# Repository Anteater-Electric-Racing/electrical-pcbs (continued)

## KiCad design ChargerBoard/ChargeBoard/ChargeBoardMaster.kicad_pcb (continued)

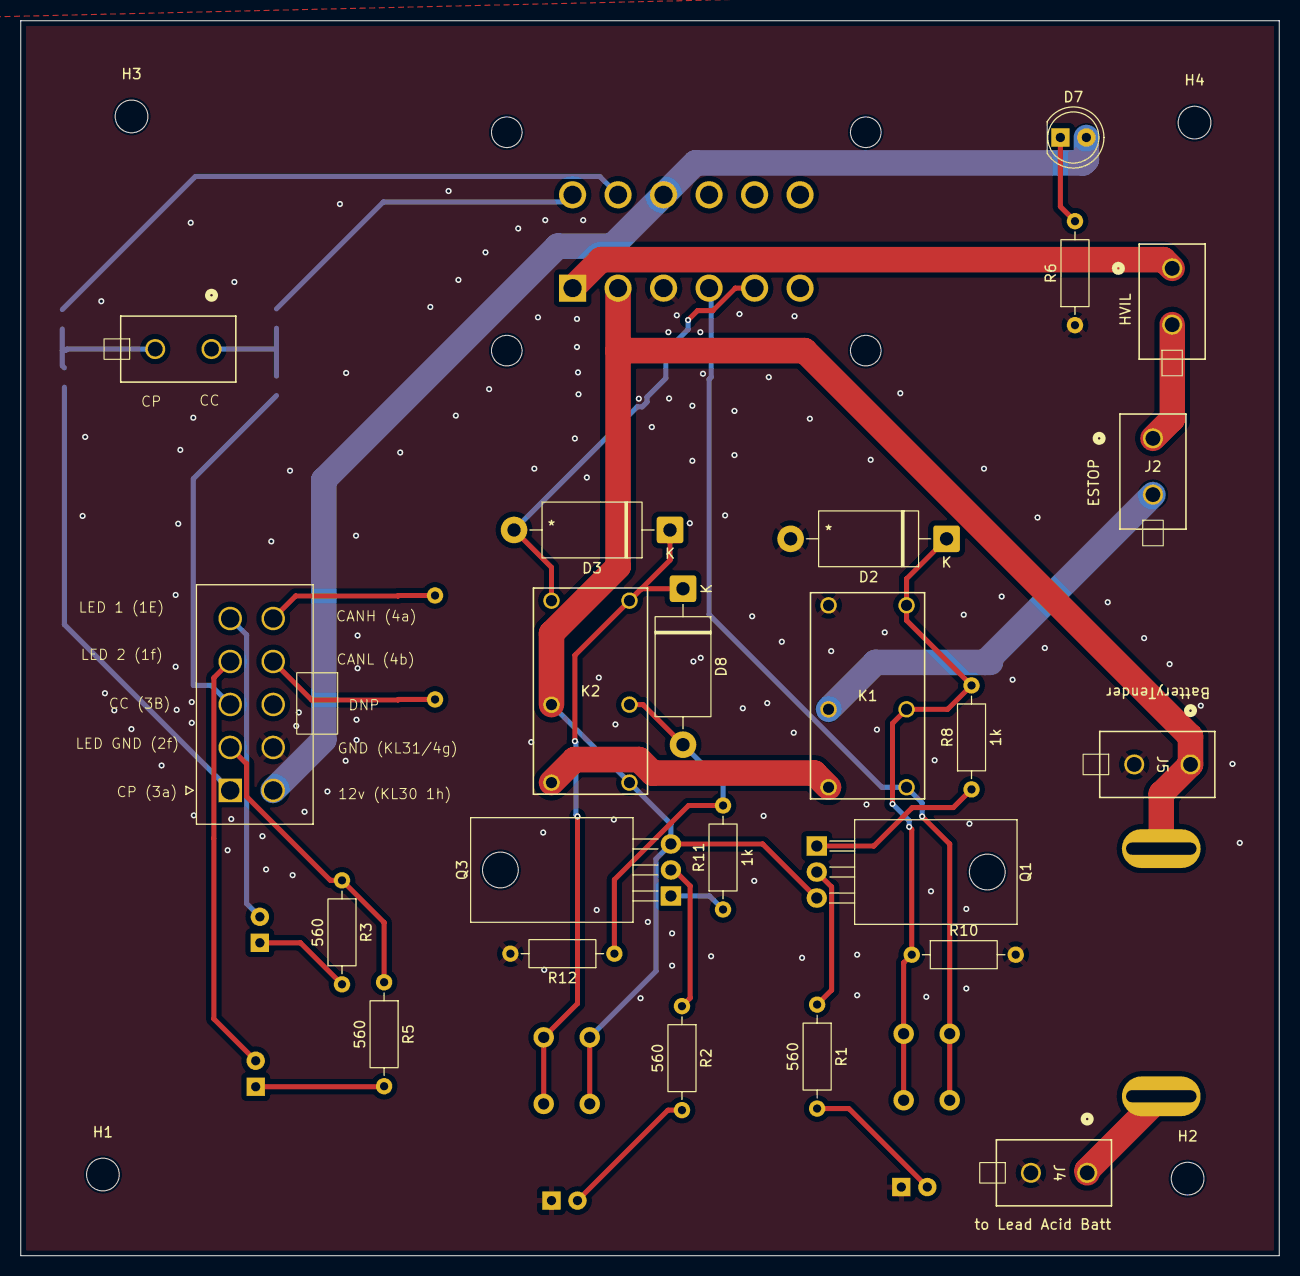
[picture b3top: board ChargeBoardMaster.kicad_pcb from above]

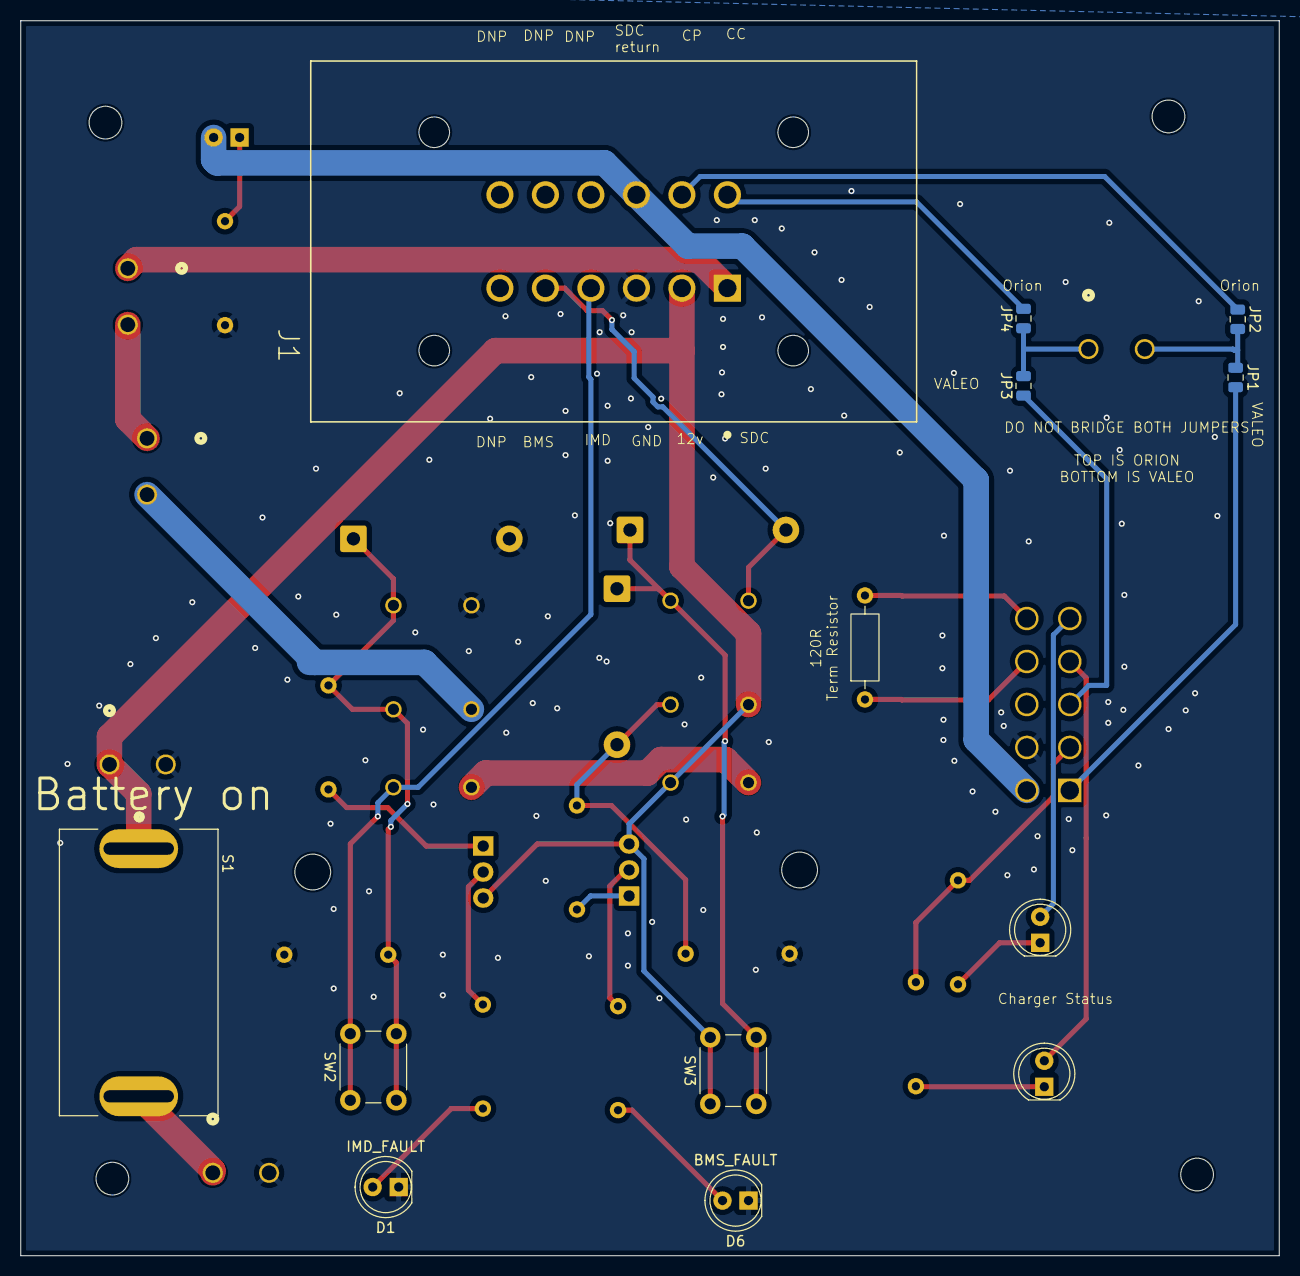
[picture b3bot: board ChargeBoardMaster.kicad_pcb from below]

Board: 2 copper layers, 123.0 x 120.7 mm, 40 parts (13 on the bottom side), 33 nets.

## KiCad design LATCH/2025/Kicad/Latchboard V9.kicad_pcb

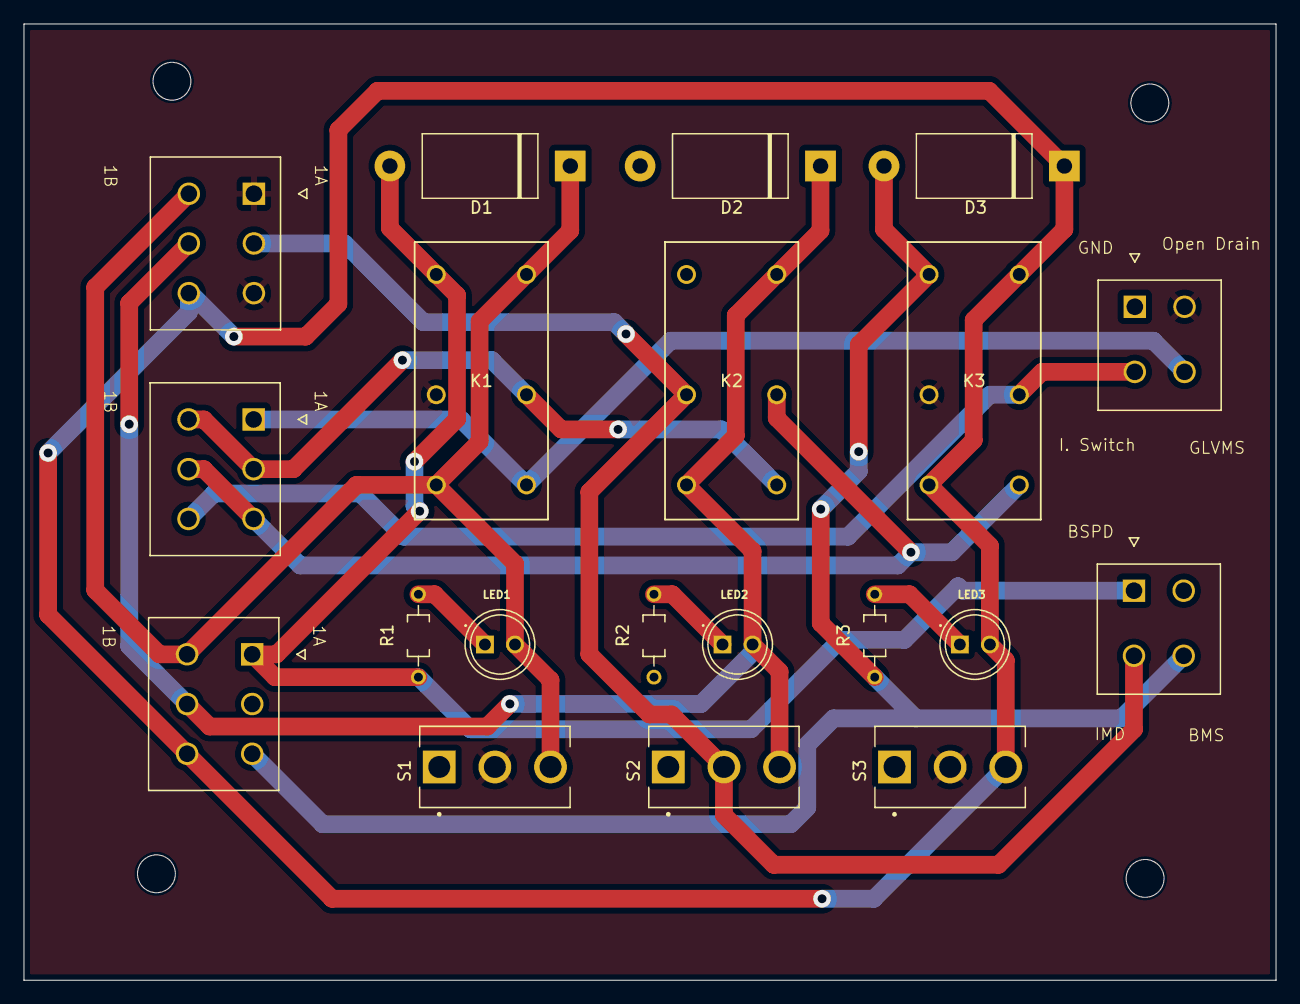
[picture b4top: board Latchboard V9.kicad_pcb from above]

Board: 2 copper layers, 105.8 x 80.8 mm, 20 parts (0 on the bottom side), 15 nets.

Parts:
D1, D2, D3: D; P2_DO-201
J1, J2: 2x2 Conn; MOLEX_39296048
J3: Relay Switch Connections; MOLEX_39288060
J4: Relay Debug Connections; MOLEX_39288060
J5: Relay LED Connections; MOLEX_39288060
K1, K2, K3: DPST Relay NO; CONN_P6B-26P_OMR
LED1, LED2, LED3: Debug LED; LED_WP7113ID
R1: THT 1k; RESAD700W45L350D185
R2, R3: THT 1K; RESAD700W45L350D185
S1, S2, S3: SPDT Switch NO; SW_100SP1T1B4M2QE

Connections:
+12V: J1.2, J3.1, J3.3, K1.3, K3.3, S1.2, S3.2
/DEBUG 1A: J1.4, J4.1, K1.5
/DEBUG 1B: J4.2, J4.4, K1.6, K2.5
/DEBUG 2B: J4.3, J4.5, K2.6, K3.5
/DEBUG 3B: J1.3, J4.6, K3.6
/LED 1B: D1.1 (K), J3.4, J5.4, K1.4, K1.8, LED1.A, S1.3
/LED 2B: D2.1 (K), J3.5, J5.5, K2.4, K2.8, LED2.A, S2.3
/LED 3B: D3.1 (K), J3.6, J5.6, K3.4, K3.8, LED3.A, S3.3
BMS FAULT: D3.2 (A), J2.4, J5.3, K3.1, R3.1
BSPD Fault: D1.2 (A), J2.1, J5.1, K1.1, R1.1
GND: D2.2 (A), J1.1, J5.2, K2.1, R2.1
IMD FAULT: J2.3, J3.2, K2.3, S2.2
unnamed: LED1.C, R1.2
unnamed: LED2.C, R2.2
unnamed: LED3.C, R3.2

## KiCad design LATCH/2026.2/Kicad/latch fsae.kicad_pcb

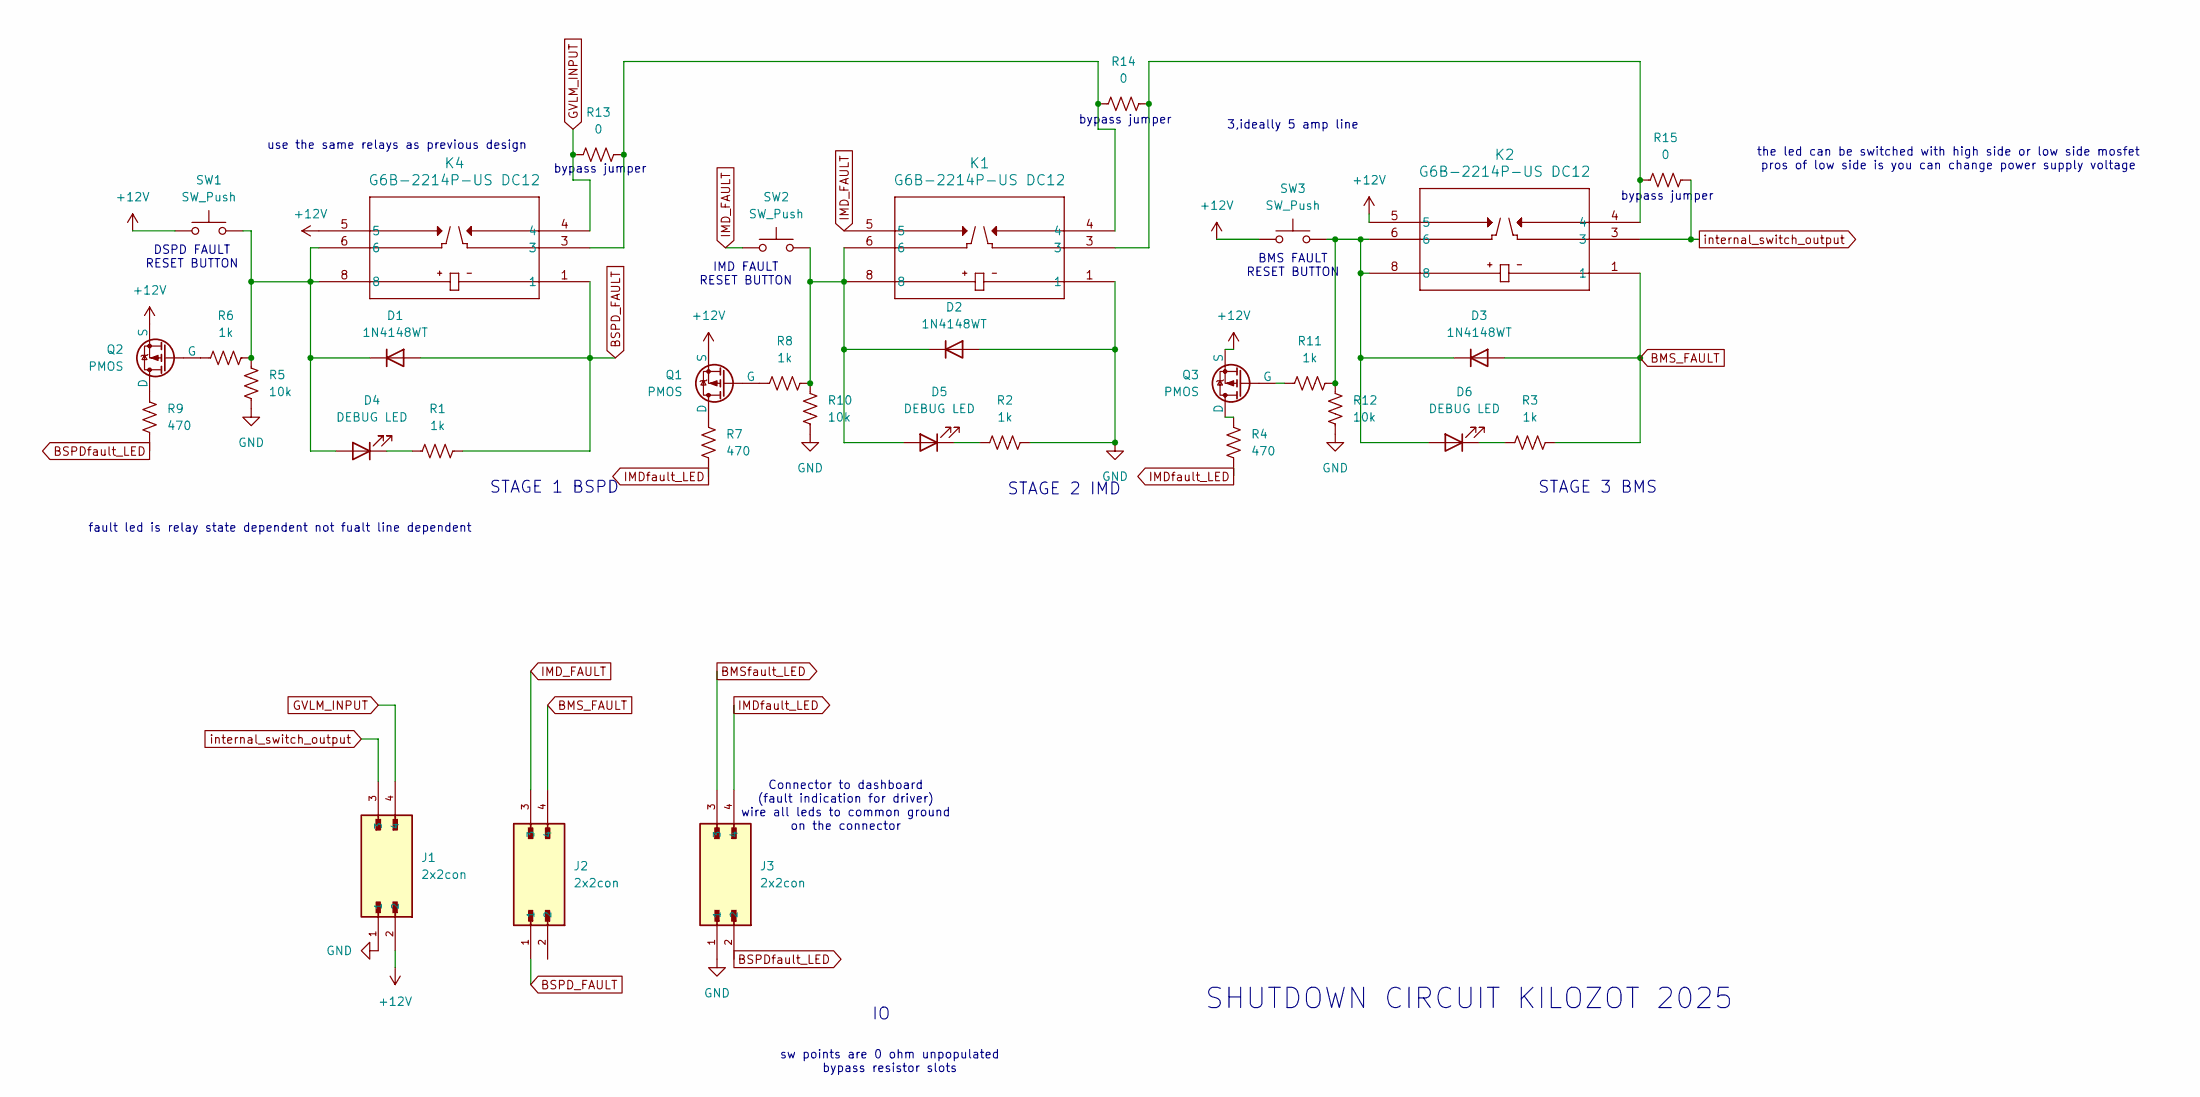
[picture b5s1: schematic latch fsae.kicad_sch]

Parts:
D1, D2, D3: 1N4148WT; D_DO-201_P15.24mm_Horizontal
D4, D5, D6: DEBUG LED; LED_D5.0mm
J1, J2, J3: 2x2con; MOLEX_39296048; PARTREV M4
K1, K2, K4: G6B-2214P-US DC12; RELAY_G6B-2114P-US_OMR
Q1, Q2, Q3: PMOS; TO-220-3_Vertical
R1, R2, R3, R6, R8, R11: 1k; R_Axial_DIN0207_L6.3mm_D2.5mm_P10.16mm_Horizontal
R4, R7, R9: 470; R_Axial_DIN0207_L6.3mm_D2.5mm_P10.16mm_Horizontal
R5, R10, R12: 10k; R_Axial_DIN0207_L6.3mm_D2.5mm_P10.16mm_Horizontal
R13, R14, R15: 0; R_Axial_DIN0207_L6.3mm_D2.5mm_P10.16mm_Horizontal
SW1, SW2, SW3: SW_Push; SW_PUSH_6mm

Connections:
+12V: J1.2, K2.5, K4.5, Q1.3 (S), Q2.3 (S), Q3.3 (S), SW1.1, SW3.1
BMS_FAULT: D3.2 (A), J2.4, K2.1, R3.2
BMSfault_LED: J3.3
BSPD_FAULT: D1.2 (A), J2.1, K4.1, R1.2
BSPDfault_LED: J3.2, R9.1
GND: D2.2 (A), J1.1, J3.1, K1.1, R2.2, R5.2, R10.2, R12.2
GVLM_INPUT: J1.4, K4.4, R13.1
IMD_FAULT: J2.3, K1.5, SW2.1
IMDfault_LED: J3.4, R4.1, R7.1
unnamed: D1.1 (K), D4.2 (A), K4.6, K4.8, R5.1, R6.1, SW1.2
unnamed: D2.1 (K), D5.2 (A), K1.6, K1.8, R8.2, R10.1, SW2.2
unnamed: D3.1 (K), D6.2 (A), K2.6, K2.8, R11.2, R12.1, SW3.2
unnamed: D4.1 (K), R1.1
unnamed: D5.1 (K), R2.1
unnamed: D6.1 (K), R3.1
unnamed: K1.3, K2.4, R14.2, R15.1
unnamed: K1.4, K4.3, R13.2, R14.1
unnamed: Q1.2 (D), R7.2
unnamed: Q1.1 (G), R8.1
unnamed: Q2.2 (D), R9.2
unnamed: Q2.1 (G), R6.2
unnamed: Q3.2 (D), R4.2
unnamed: Q3.1 (G), R11.1
internal_switch_output: J1.3, K2.3, R15.2

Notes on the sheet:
Connector to dashboard (fault indication for driver) wire all leds to common ground on the connector
3,ideally 5 amp line
bypass jumper
DSPD FAULT RESET BUTTON
the led can be switched with high side or low side mosfet pros of low side is you can change power supply voltage
fault led is relay state dependent not fualt line dependent
STAGE 1 BSPD
sw points are 0 ohm unpopulated bypass resistor slots
SHUTDOWN CIRCUIT KILOZOT 2025
use the same relays as previous design
IMD FAULT RESET BUTTON
STAGE 3 BMS
STAGE 2 IMD
BMS FAULT RESET BUTTON

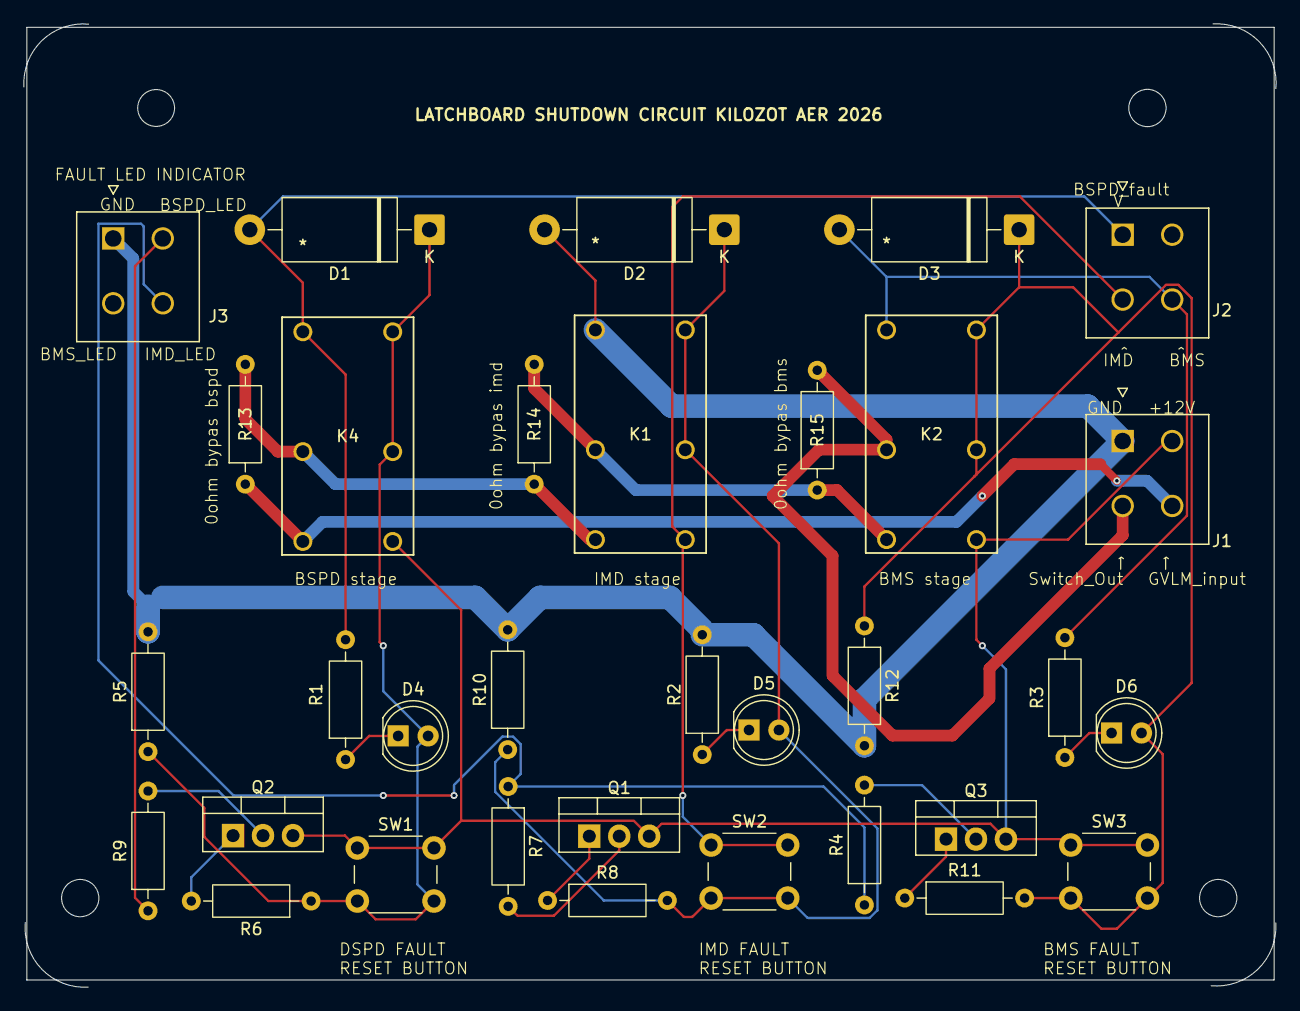
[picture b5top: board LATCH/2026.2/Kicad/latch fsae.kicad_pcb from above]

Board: 2 copper layers, 106.2 x 81.7 mm, 33 parts (0 on the bottom side), 23 nets.

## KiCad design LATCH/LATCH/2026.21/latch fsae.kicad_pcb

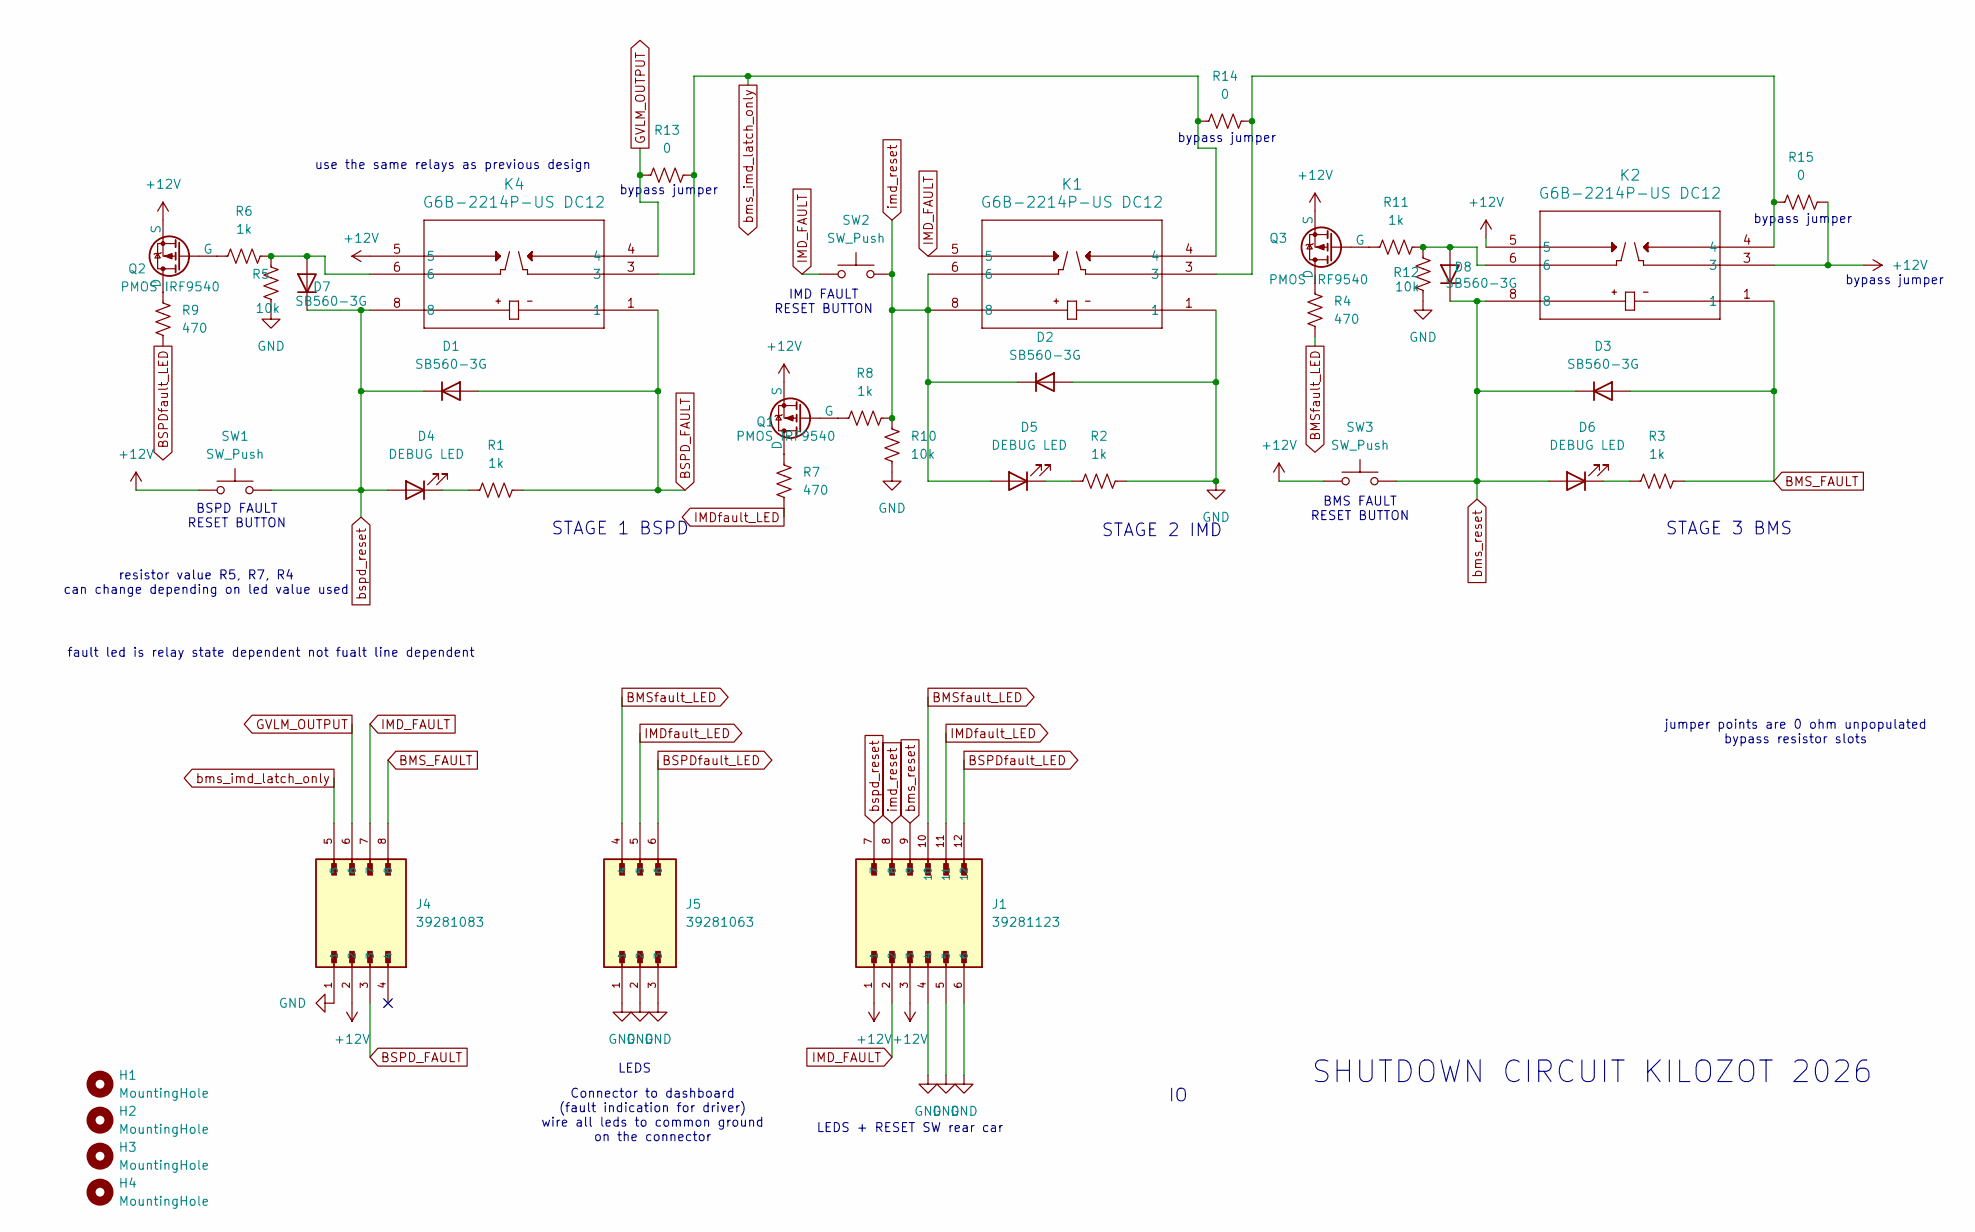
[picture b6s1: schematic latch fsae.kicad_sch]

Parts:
D1, D2, D3, D7, D8: SB560-3G; D_DO-201_P15.24mm_Horizontal
D4, D5, D6: DEBUG LED; LED_D5.0mm
H1, H2, H3, H4: MountingHole; MountingHole_3.2mm_M3
J1: 39281123; MOLEX_39281123; PARTREV M4
J4: 39281083; MOLEX_39281083; PARTREV M4
J5: 39281063; MOLEX_39281063; PARTREV M4
K1, K2, K4: G6B-2214P-US DC12; RELAY_G6B-2114P-US_OMR
Q1, Q2, Q3: PMOS IRF9540; TO-220-3_Vertical
R1, R2, R3, R6, R8, R11: 1k; R_Axial_DIN0207_L6.3mm_D2.5mm_P10.16mm_Horizontal
R4, R7, R9: 470; R_Axial_DIN0207_L6.3mm_D2.5mm_P10.16mm_Horizontal
R5, R10, R12: 10k; R_Axial_DIN0207_L6.3mm_D2.5mm_P10.16mm_Horizontal
R13, R14, R15: 0; R_Axial_DIN0207_L6.3mm_D2.5mm_P10.16mm_Horizontal
SW1, SW2, SW3: SW_Push; SW_PUSH_6mm

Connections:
+12V: J1.1, J1.3, J4.2, K2.3, K2.5, K4.5, Q1.3 (S), Q2.3 (S), Q3.3 (S), R15.2, SW1.1, SW3.1
BMS_FAULT: D3.2 (A), J4.8, K2.1, R3.2
BMSfault_LED: J1.10, J5.4, R4.1
BSPD_FAULT: D1.2 (A), J4.3, K4.1, R1.2
BSPDfault_LED: J1.12, J5.6, R9.1
GND: D2.2 (A), J1.4, J1.5, J1.6, J4.1, J5.1, J5.2, J5.3, K1.1, R2.2, R5.2, R10.2, R12.2
GVLM_OUTPUT: J4.6, K4.4, R13.1
IMD_FAULT: J1.2, J4.7, K1.5, SW2.1
IMDfault_LED: J1.11, J5.5, R7.1
unnamed: D4.1 (K), R1.1
unnamed: D5.1 (K), R2.1
unnamed: D6.1 (K), R3.1
unnamed: D7.2 (A), K4.6, R5.1, R6.2
unnamed: D8.2 (A), K2.6, R11.2, R12.1
unnamed: K1.3, K2.4, R14.2, R15.1
unnamed: Q1.2 (D), R7.2
unnamed: Q1.1 (G), R8.1
unnamed: Q2.2 (D), R9.2
unnamed: Q2.1 (G), R6.1
unnamed: Q3.2 (D), R4.2
unnamed: Q3.1 (G), R11.1
bms_imd_latch_only: J4.5, K1.4, K4.3, R13.2, R14.1
bms_reset: D3.1 (K), D6.2 (A), D8.1 (K), J1.9, K2.8, SW3.2
bspd_reset: D1.1 (K), D4.2 (A), D7.1 (K), J1.7, K4.8, SW1.2
imd_reset: D2.1 (K), D5.2 (A), J1.8, K1.6, K1.8, R8.2, R10.1, SW2.2

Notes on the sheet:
Connector to dashboard (fault indication for driver) wire all leds to common ground on the connector
BSPD FAULT RESET BUTTON
bypass jumper
fault led is relay state dependent not fualt line dependent
STAGE 1 BSPD
jumper points are 0 ohm unpopulated bypass resistor slots
resistor value R5, R7, R4 can change depending on led value used
SHUTDOWN CIRCUIT KILOZOT 2026
use the same relays as previous design
IMD FAULT RESET BUTTON
LEDS
STAGE 3 BMS
STAGE 2 IMD
LEDS + RESET SW rear car
BMS FAULT RESET BUTTON

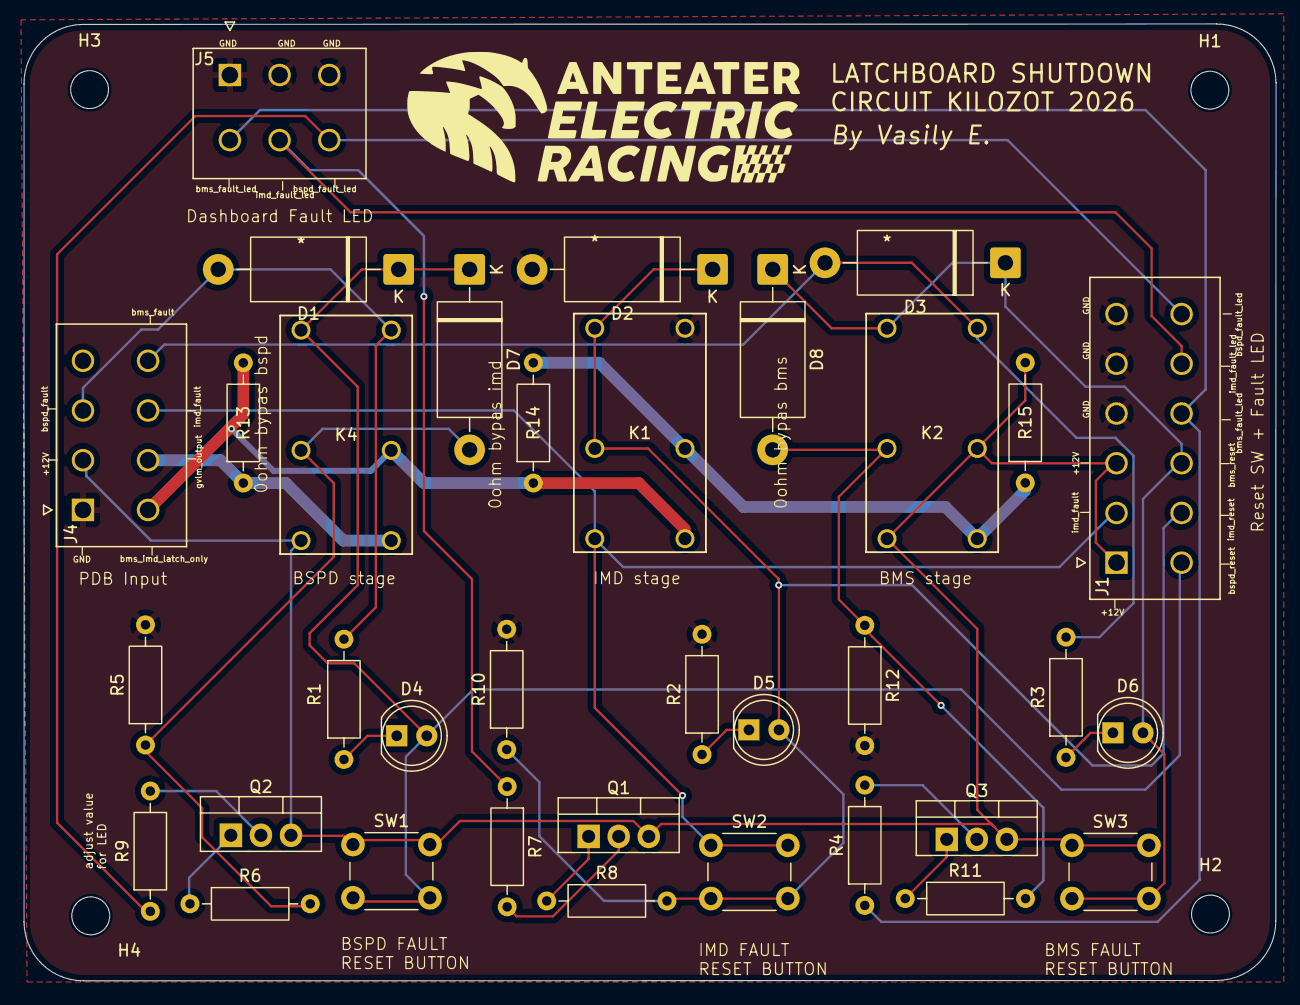
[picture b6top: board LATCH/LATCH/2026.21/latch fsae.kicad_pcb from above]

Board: 2 copper layers, 105.8 x 80.8 mm, 39 parts (0 on the bottom side), 25 nets.

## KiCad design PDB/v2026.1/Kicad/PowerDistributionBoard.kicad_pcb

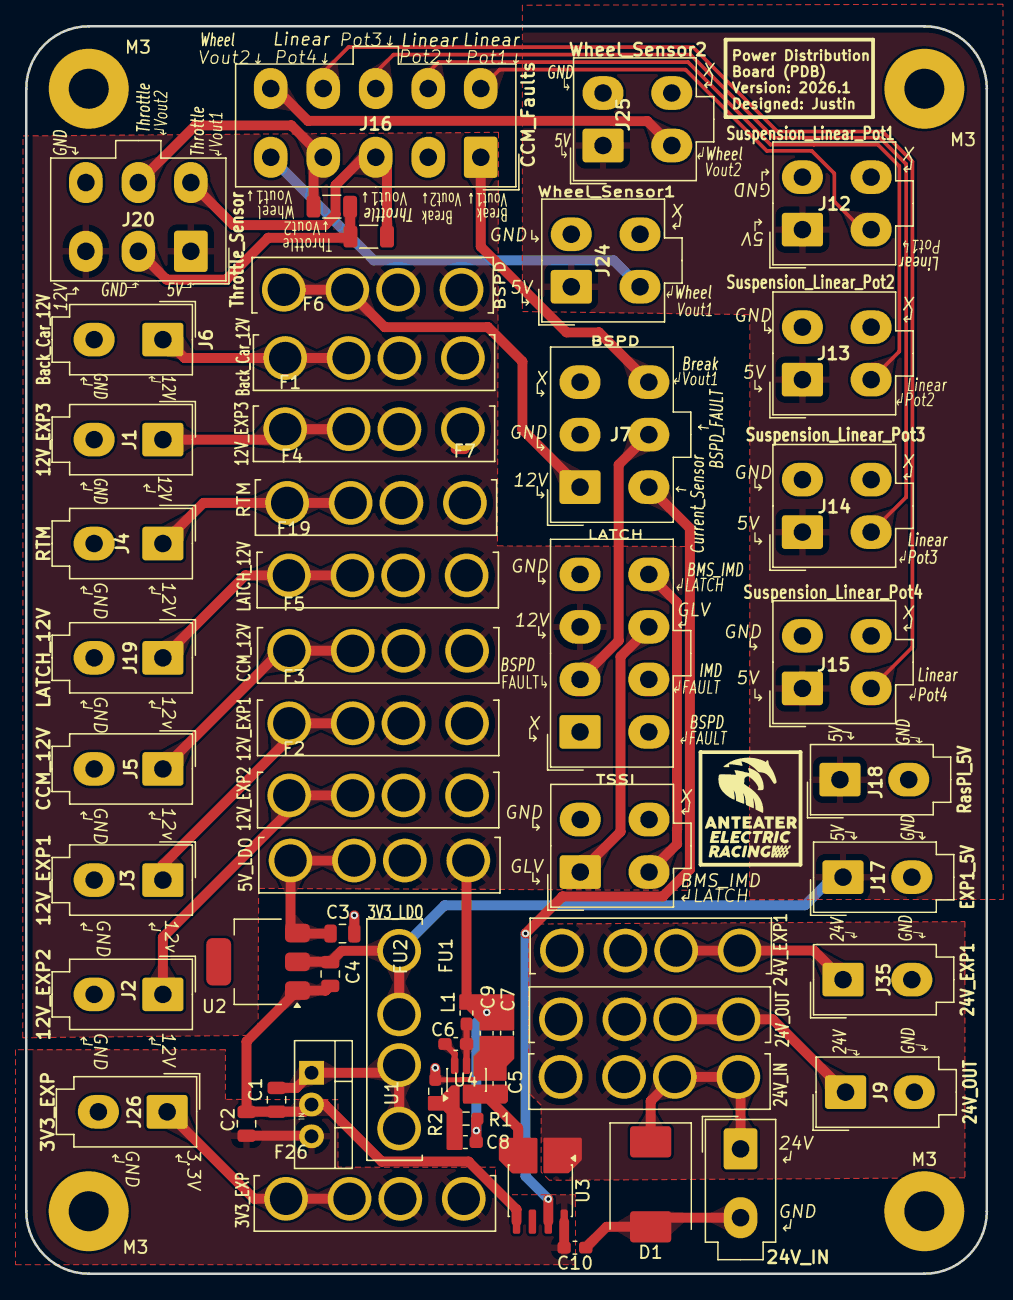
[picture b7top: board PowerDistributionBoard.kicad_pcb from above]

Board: 2 copper layers, 76.8 x 99.8 mm, 62 parts (0 on the bottom side), 36 nets.

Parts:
C1: 0.47uF; C_0805_2012Metric
C2: 33uF; C_0805_2012Metric
C3: 1uF; C_0805_2012Metric
C4: 2.2uF; C_0805_2012Metric
C5: 10uF; C_0603_1608Metric_Pad1.08x0.95mm_HandSolder
C6, C10: 100nF; C_0603_1608Metric_Pad1.08x0.95mm_HandSolder
C7, C9: 22uF; C_0603_1608Metric_Pad1.08x0.95mm_HandSolder
C8: 56pF; C_0603_1608Metric_Pad1.08x0.95mm_HandSolder
D1: 1.5SMCxxA; D_SMC
F1: 12V_EXP3; FUSE_3522-2
F2: 12V_EXP2; FUSE_3522-2
F3: 12V_EXP1; FUSE_3522-2
F4: RTM; FUSE_3522-2
F5: CCM_12V; FUSE_3522-2
F6: Back_Car_12V; FUSE_3522-2
F7: BSPD; FUSE_3522-2
F8: 24V_OUT; FUSE_3522-2
F9: 24V_IN; FUSE_3522-2
F19: LATCH_12V; FUSE_3522-2
F26: 3V3_EXP; FUSE_3522-2
F35: 24V_EXP1; FUSE_3522-2
FU1: 3V3_LDO; FUSE_3522-2
FU2: 5V_LDO; FUSE_3522-2
J1: 12V_EXP3; Molex_Mini-Fit_Jr_5566-02A_2x01_P4.20mm_Vertical
J2: 12V_EXP2; Molex_Mini-Fit_Jr_5566-02A_2x01_P4.20mm_Vertical
J3: 12V_EXP1; Molex_Mini-Fit_Jr_5566-02A_2x01_P4.20mm_Vertical
J4: RTM; Molex_Mini-Fit_Jr_5566-02A_2x01_P4.20mm_Vertical
J5: CCM_12V; Molex_Mini-Fit_Jr_5566-02A_2x01_P4.20mm_Vertical
J6: Back_Car_12V; Molex_Mini-Fit_Jr_5566-02A_2x01_P4.20mm_Vertical
J7: BSPD; Molex_Mini-Fit_Jr_5566-06A_2x03_P4.20mm_Vertical
J8: TSSI; Molex_Mini-Fit_Jr_5566-04A_2x02_P4.20mm_Vertical
J9: 24V_OUT; Molex_Mini-Fit_Jr_5566-02A_2x01_P4.20mm_Vertical
J10: 24V_IN; Molex_Mini-Fit_Jr_5566-02A_2x01_P4.20mm_Vertical
J11: LATCH; Molex_Mini-Fit_Jr_5566-08A_2x04_P4.20mm_Vertical
J12: Suspension_Linear_Pot1; Molex_Mini-Fit_Jr_5566-04A_2x02_P4.20mm_Vertical
J13: Suspension_Linear_Pot2; Molex_Mini-Fit_Jr_5566-04A_2x02_P4.20mm_Vertical
J14: Suspension_Linear_Pot3; Molex_Mini-Fit_Jr_5566-04A_2x02_P4.20mm_Vertical
J15: Suspension_Linear_Pot4; Molex_Mini-Fit_Jr_5566-04A_2x02_P4.20mm_Vertical
J16: CCM_Faults; Molex_Mini-Fit_Jr_5566-10A_2x05_P4.20mm_Vertical
J17: EXP1_5V; Molex_Mini-Fit_Jr_5566-02A_2x01_P4.20mm_Vertical
J18: RasPI_5V; Molex_Mini-Fit_Jr_5566-02A_2x01_P4.20mm_Vertical
J19: LATCH_12V; Molex_Mini-Fit_Jr_5566-02A_2x01_P4.20mm_Vertical
J20: Throttle_Sensor; Molex_Mini-Fit_Jr_5566-06A_2x03_P4.20mm_Vertical
J24: Wheel_Sensor1; Molex_Mini-Fit_Jr_5566-04A_2x02_P4.20mm_Vertical
J25: Wheel_Sensor2; Molex_Mini-Fit_Jr_5566-04A_2x02_P4.20mm_Vertical
J26: 3V3_EXP; Molex_Mini-Fit_Jr_5566-02A_2x01_P4.20mm_Vertical
J35: 24V_EXP1; Molex_Mini-Fit_Jr_5566-02A_2x01_P4.20mm_Vertical
L1: 10uH; L_0603_1608Metric_Pad1.05x0.95mm_HandSolder
M3, M3#2, M3#3, M3#4: MountingHole M3; MountingHole_3.2mm_M3_Pad
R1: 249k; R_0603_1608Metric_Pad0.98x0.95mm_HandSolder
R2: 18k; R_0603_1608Metric_Pad0.98x0.95mm_HandSolder
R3, R4: 10K; R_1206_3216Metric
U1: 5to3.3_Linear_Regulator; TO-220-3_Vertical
U2: TLV76150DCYR; SOT-223
U3: ACS711xLCTR-12AB; SOIC-8_3.9x4.9mm_P1.27mm
U4: AP63200WU; TSOT-23-6

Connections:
3.3V: C2.1, C10.2, F26.2, U1.3 (VO), U3.8 (VCC)
5V: C4.1, FU1.1, J12.1, J13.1, J14.1, J15.1, J17.1, J18.1, J24.1, J25.1, U2.2 (OUT)
12V: C7.1, C8.1, C9.1, F1.2, F2.2, F3.2, F4.2, F5.2, F6.2, F7.1, F19.2, FU2.2, J11.3, J20.1, J20.3, L1.2, R1.1
24V: F8.2, F9.1, F35.2, U3.1 (IP+), U3.2 (IP+)
/BST: C6.2, U4.6 (BST)
/BUCK_IN: C5.1, U3.3 (IP-), U3.4 (IP-), U4.2 (EN), U4.3 (IN)
/Back_Car_12V: F6.1, J6.1
/FB: C8.2, R1.2, R2.1, U4.1 (FB)
/Fuse_5to3.3: C1.1, FU1.2, U1.1 (VI)
/Fuse_12to5: C3.1, FU2.1, U2.3 (IN)
/Fuse_24V_OUT: F8.1, J9.1
/Fuse_BSPD: F7.2, J7.1
/Fuse_CCM_12V: F5.1, J5.1
/Fuse_EXP1_12V: F3.1, J3.1
/Fuse_EXP1_24V: F35.1, J35.1
/Fuse_EXP2_12V: F2.1, J2.1
/Fuse_EXP3_12V: F1.1, J1.1
/Fuse_EXP_3V3: F26.1, J26.1
/Fuse_LATCH_12V: F19.1, J19.1
/Fuse_RTM: F4.1, J4.1
/SW: C6.1, L1.1, U4.5 (SW)
BSPD_FAULT: J7.5, J11.2
Brake_Sensor_Vout1: J7.6, J16.1
Current_Sensor: J7.4, U3.7 (VIOUT)
GLV: J8.1, J11.7
GND: C1.2, C2.2, C3.2, C4.2, C5.2, C7.2, C9.2, C10.1, D1.2 (A2), J1.2, J2.2, J3.2, J4.2, J5.2, J6.2, J7.2, J8.2, J9.2, J10.2, J11.4, J12.2, J13.2, J14.2, J15.2, J17.2, J18.2, J19.2, J20.2, J20.6, J24.2, J25.2, J26.2, J35.2, R2.2, R3.2, R4.2, U1.2 (GND), U2.1 (GND), U3.5 (GND), U4.4 (GND)
Linear_Pot1: J12.3, J16.6
Linear_Pot2: J13.3, J16.7
Linear_Pot3: J14.3, J16.8
Linear_Pot4: J15.3, J16.9
unnamed: D1.1 (A1), F9.2, J10.1
Throttle_Sensor_Vout1: J16.3, J20.4, R3.1
Throttle_Sensor_Vout2: J16.4, J20.5, R4.1
Wheel_Sensor_Vout1: J16.5, J24.3
Wheel_Sensor_Vout2: J16.10, J25.3
bms_imd_latch_only: J8.3, J11.8
